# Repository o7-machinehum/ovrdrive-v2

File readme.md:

Phantomdrive is open source encrypted USB drive with a stealth mechanism to hide its second partition. To decrypt it you must create a file called unlock.txt containing your password in the format `password:addpasswordhere`, this is used to derive a AES-256 key. The drive automatically unmounts itself, remounts the remaining disk and encrypts and decrypts in place. It uses CH569W SoC, which has USB3, SDIO and an AES hardware block. It is programmable over USB using the `wch-ch56x-isp` library.

``` bash
|-- ee             # Hardware files
|-- Makefile
|-- readme.md      # This files
|-- test           # Test the cypto components
|-- ref            # Reference docs
|-- src            # Firmware
|-- tests          # Verification scripts
|-- wch-ch56x-bsp  # Board support package
`-- wch-ch56x-isp  # Programming software
```

# Getting Started
``` bash
git submodule update --init --recursive --checkout --force
cd wch-ch56x-isp
make # Build the ISP tool
```

## Install the toolchain
The HydraUSB3 project requires a patched GCC that supports the
`WCH-Interrupt-fast` interrupt attribute. Download the xpack GCC from the HydraUSB3 project:

```bash
cd /tmp
curl -sL -o riscv-gcc-xpack.tar.gz \
  "https://github.com/hydrausb3/riscv-none-elf-gcc-xpack/releases/download/12.2.0-1/xpack-riscv-none-elf-gcc-12.2.0-1-linux-x64.tar.gz"
tar xzf riscv-gcc-xpack.tar.gz
sudo cp -r xpack-riscv-none-elf-gcc-12.2.0-1/* /usr/local/
```

## Debugging
```
make UART=1 # Enable UART
make UART=1 DEBUG_USB=1 # Enable USB Debugging
```

## Build and Flashing the project
``` bash
make
# Remove flash drive
# While holding boot button, plug in
./wch-ch56x-isp/wch-ch56x-isp -d=off # This is needed just one to disable debug mode
make flash
```

## Unlocking Drive
``` bash
sudo echo "password:YourPasswordHere13245" > /mnt/unlock.txt
```

# Releasing the hardware
``` bash
./scripts/release_hardware.sh
```

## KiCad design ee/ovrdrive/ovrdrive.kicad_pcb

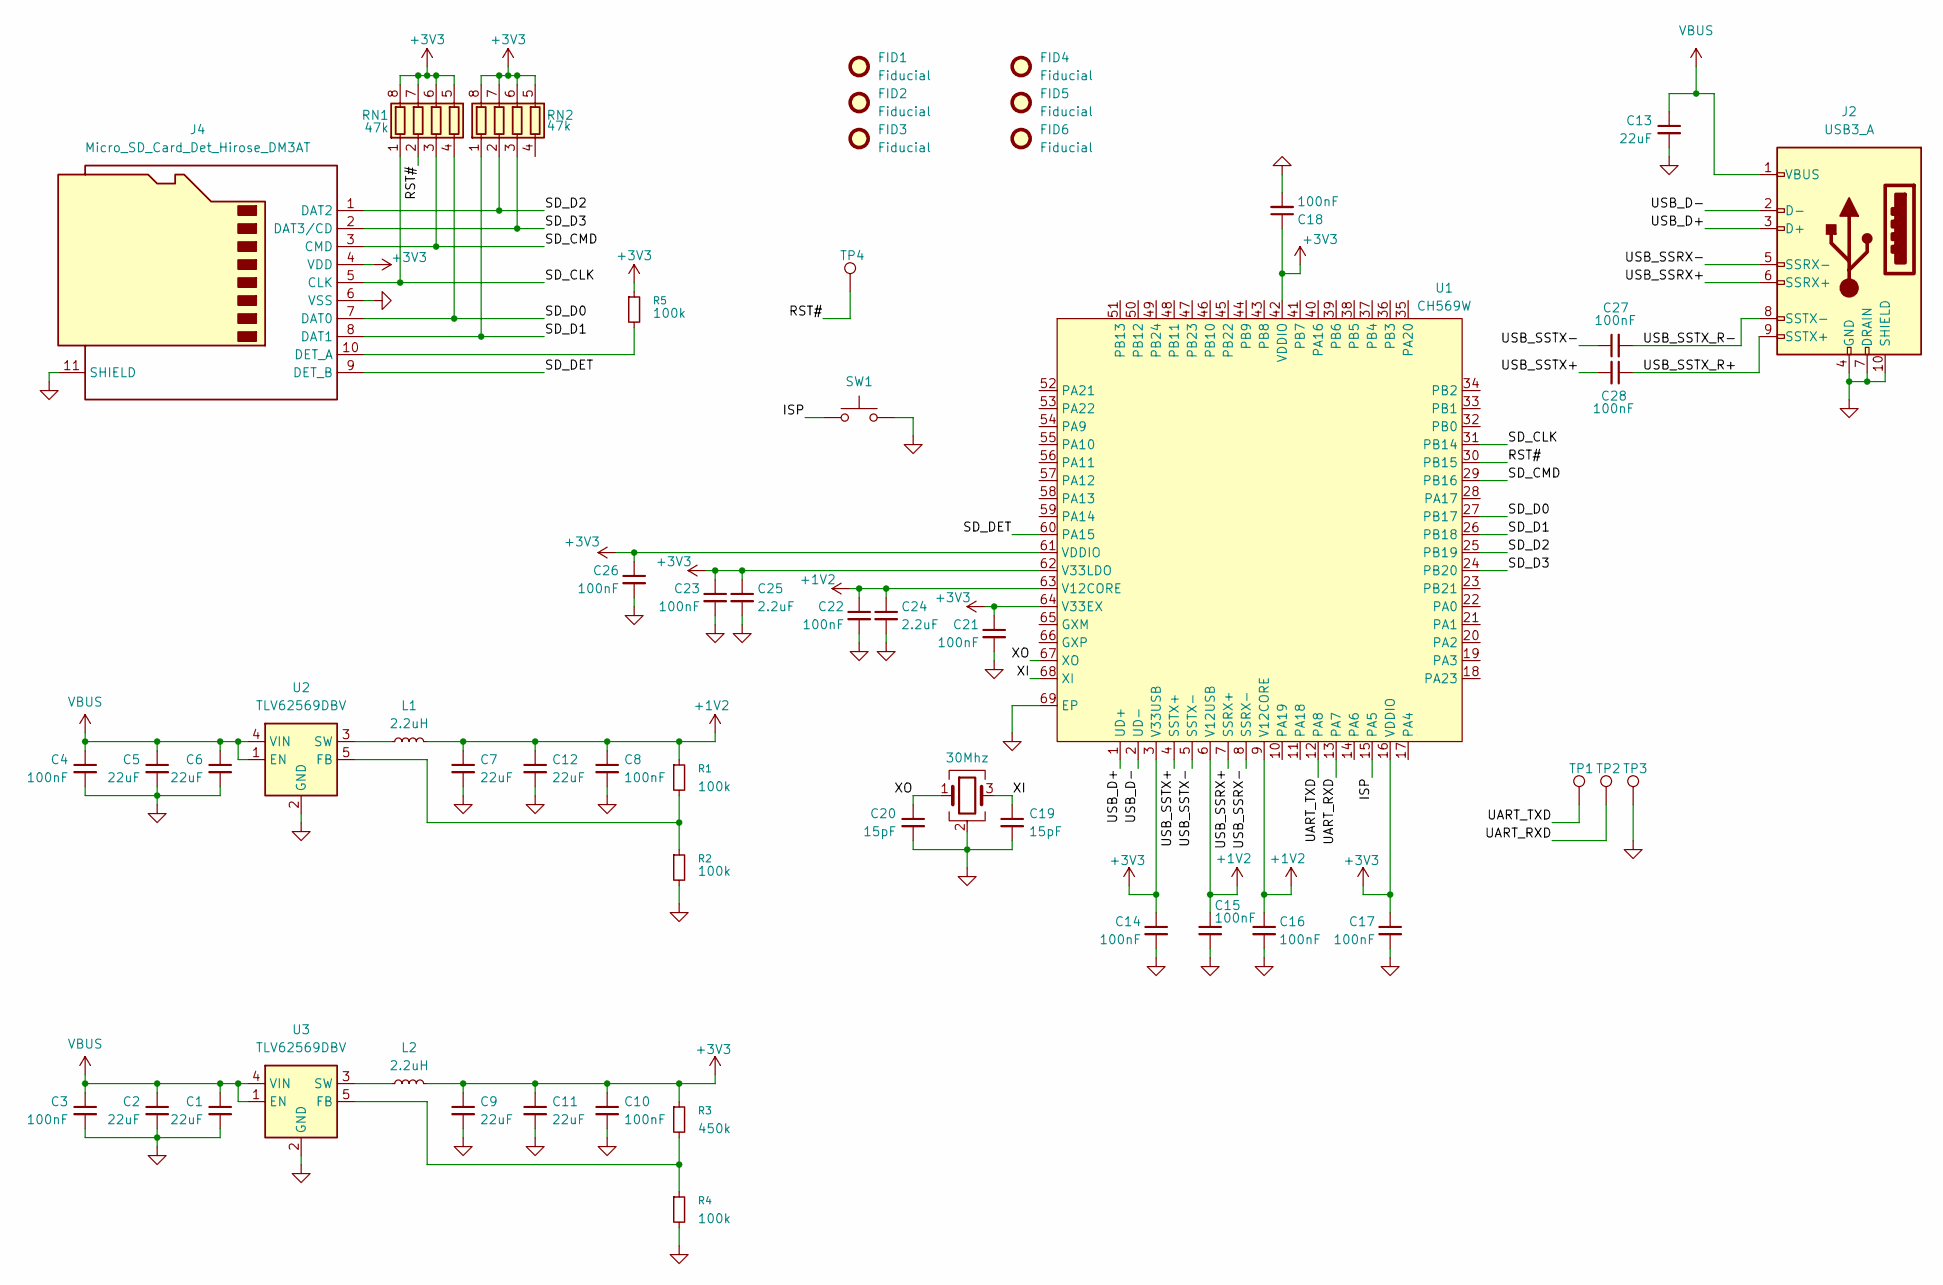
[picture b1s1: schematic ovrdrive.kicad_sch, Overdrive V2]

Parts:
C1, C2, C5, C6, C7, C9, C11, C12, C13: 22uF; C_0402_1005Metric; MPN CL05A226MQ5N6J8
C3, C4, C8, C10, C14, C15, C16, C17, C18, C21, C22, C23, C26, C27, C28: 100nF; C_0402_1005Metric; MPN CL05B104KP5NNNC
C19, C20: 15pF; C_0402_1005Metric; MPN CL05C150JB5NNNC
C24, C25: 2.2uF; C_0402_1005Metric; MPN CL05A225MQ5NNNC
FID1, FID2, FID3, FID4, FID5, FID6: Fiducial; Fiducial_0.5mm_Mask1mm; MPN DNP
J2: USB3_A; USB3_A_Plug_Wuerth_692112030100_Horizontal; MPN 692112030100
J4: Micro_SD_Card_Det_Hirose_DM3AT; microSD_HC_Hirose_DM3AT-SF-PEJM5; MPN DM3AT-SF-PEJM5
L1, L2: 2.2uH; L_Changjiang_FTC303015D; MPN SRN3015-2R2M
R1, R2, R4, R5: 100k; C_0402_1005Metric; MPN RC0402FR-07100KL
R3: 450k; C_0402_1005Metric; MPN RC0402FR-07453KL
RN1, RN2: 47k; R_Array_Concave_4x0402; MPN CAT10-473J4LF
SW1: SW_Push; SW_Push_SPST_NO_Alps_SKRK; MPN SKRKAEE020
TP1, TP2, TP3, TP4: TestPoint; TestPoint_Pad_1.0x1.0mm; MPN DNP
U1: CH569W; QFN-68-1EP_8x8mm_P0.4mm_EP5.2x5.2mm; MPN CH569W
U2, U3: TLV62569DBV; SOT-23-5; MPN TLV62569DBV
Y2: 30Mhz; Crystal_SMD_3225-4Pin_3.2x2.5mm; MPN ABM8-30.000MHZ-12-B1U-T

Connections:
+1V2: C7.1, C8.1, C12.1, C15.1, C16.1, C22.1, C24.1, L1.2, R1.1, U1.6 (V12USB), U1.9 (V12CORE), U1.63 (V12CORE)
+3V3: C9.1, C10.1, C11.1, C14.1, C17.1, C18.1, C21.1, C23.1, C25.1, C26.1, J4.4 (VDD), L2.2, R3.1, R5.1, RN1.5 (R4.2), RN1.6 (R3.2), RN1.7 (R2.2), RN1.8 (R1.2), RN2.5 (R4.2), RN2.6 (R3.2), RN2.7 (R2.2), RN2.8 (R1.2), U1.3 (V33USB), U1.16 (VDDIO), U1.42 (VDDIO), U1.61 (VDDIO), U1.62 (V33LDO), U1.64 (V33EX)
/ISP: SW1.1, U1.15 (PA5)
/RST#: RN1.2 (R2.1), TP4.1 (1_1), U1.30 (PB15)
/SD_CLK: J4.5 (CLK), RN1.1 (R1.1), U1.31 (PB14)
/SD_CMD: J4.3 (CMD), RN1.3 (R3.1), U1.29 (PB16)
/SD_D0: J4.7 (DAT0), RN1.4 (R4.1), U1.27 (PB17)
/SD_D1: J4.8 (DAT1), RN2.1 (R1.1), U1.26 (PB18)
/SD_D2: J4.1 (DAT2), RN2.2 (R2.1), U1.25 (PB19)
/SD_D3: J4.2 (DAT3/CD), RN2.3 (R3.1), U1.24 (PB20)
/SD_DET: J4.9 (DET_B), U1.60 (PA15)
/UART_RXD: TP2.1 (1_1), U1.13 (PA7)
/UART_TXD: TP1.1 (1_1), U1.12 (PA8)
/USB_D+: J2.3 (D+), U1.1 (UD+)
/USB_D-: J2.2 (D-), U1.2 (UD-)
/USB_SSRX+: J2.6 (SSRX+), U1.7 (SSRX+)
/USB_SSRX-: J2.5 (SSRX-), U1.8 (SSRX-)
/USB_SSTX+: C28.2, U1.4 (SSTX+)
/USB_SSTX-: C27.1, U1.5 (SSTX-)
/USB_SSTX_R+: C28.1, J2.9 (SSTX+)
/USB_SSTX_R-: C27.2, J2.8 (SSTX-)
/XI: C19.1, U1.68 (XI), Y2.3
/XO: C20.1, U1.67 (XO), Y2.1
GND: C1.2, C2.2, C3.2, C4.2, C5.2, C6.2, C7.2, C8.2, C9.2, C10.2, C11.2, C12.2, C13.2, C14.2, C15.2, C16.2, C17.2, C18.2, C19.2, C20.2, C21.2, C22.2, C23.2, C24.2, C25.2, C26.2, J2.4 (GND), J2.7 (DRAIN), J2.10 (SHIELD), J4.6 (VSS), J4.11 (SHIELD), R2.2, R4.2, SW1.2, TP3.1 (1_1), U1.69 (EP), U2.2 (GND), U3.2 (GND), Y2.2 (G), Y2.4 (G)
unnamed: J4.10 (DET_A), R5.2
unnamed: R1.2, R2.1, U2.5 (FB)
unnamed: L1.1, U2.3 (SW)
unnamed: R3.2, R4.1, U3.5 (FB)
unnamed: L2.1, U3.3 (SW)
VBUS: C1.1, C2.1, C3.1, C4.1, C5.1, C6.1, C13.1, J2.1 (VBUS), U2.1 (EN), U2.4 (VIN), U3.1 (EN), U3.4 (VIN)

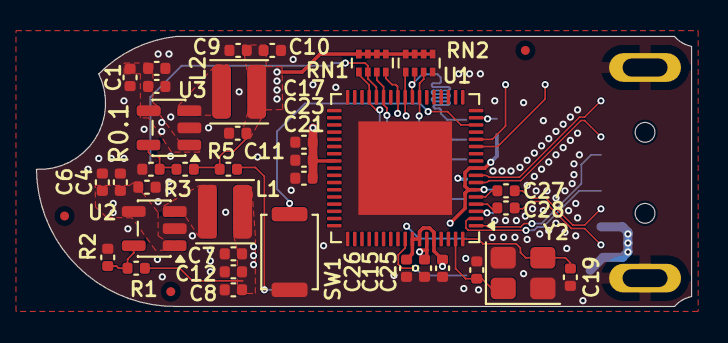
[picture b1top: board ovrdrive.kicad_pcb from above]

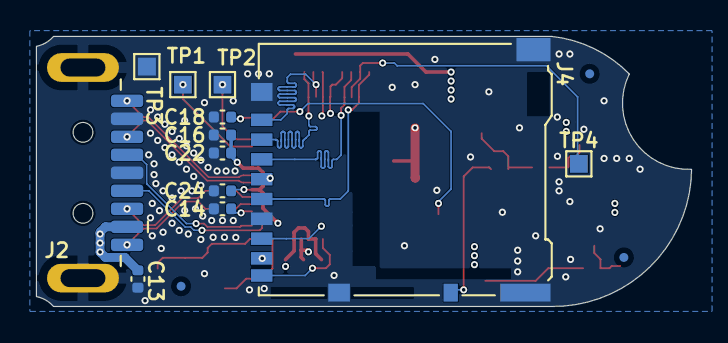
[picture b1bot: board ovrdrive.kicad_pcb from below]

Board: 4 copper layers, 36.4 x 15.0 mm, 54 parts (15 on the bottom side), 30 nets.

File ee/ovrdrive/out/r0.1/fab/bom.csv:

"Designator","Value","Footprint","Quantity","Part Number"
"C1,C2,C5-C7,C9,C11-C13","22uF","Capacitor_SMD:C_0402_1005Metric","9","CL05A226MQ5N6J8"
"C3,C4,C8,C10,C14-C18,C21-C23,C26-C28","100nF","Capacitor_SMD:C_0402_1005Metric","15","CL05B104KP5NNNC"
"C19,C20","15pF","Capacitor_SMD:C_0402_1005Metric","2","CL05C150JB5NNNC"
"C24,C25","2.2uF","Capacitor_SMD:C_0402_1005Metric","2","CL05A225MQ5NNNC"
"J2","USB3_A","Connector_USB:USB3_A_Plug_Wuerth_692112030100_Horizontal","1","692112030100"
"J4","Micro_SD_Card_Det_Hirose_DM3AT","Connector_Card:microSD_HC_Hirose_DM3AT-SF-PEJM5","1","DM3AT-SF-PEJM5"
"L1,L2","2.2uH","Inductor_SMD:L_Changjiang_FTC303015D","2","SRN3015-2R2M"
"R1,R2,R4,R5","100k","Capacitor_SMD:C_0402_1005Metric","4","RC0402FR-07100KL"
"R3","450k","Capacitor_SMD:C_0402_1005Metric","1","RC0402FR-07453KL"
"RN1,RN2","47k","Resistor_SMD:R_Array_Concave_4x0402","2","CAT10-473J4LF"
"SW1","SW_Push","Button_Switch_SMD:SW_Push_SPST_NO_Alps_SKRK","1","SKRKAEE020"
"U1","CH569W","Package_DFN_QFN:QFN-68-1EP_8x8mm_P0.4mm_EP5.2x5.2mm","1","CH569W"
"U2,U3","TLV62569DBV","Package_TO_SOT_SMD:SOT-23-5","2","TLV62569DBV"
"Y2","30Mhz","Crystal:Crystal_SMD_3225-4Pin_3.2x2.5mm","1","ABM8-30.000MHZ-12-B1U-T"

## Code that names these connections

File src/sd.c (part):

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 * (CMD17/18 for read, CMD24/25 for write).
 *
 * Hardware interface:
 *   CLK  = PB15 (bSDCK)          - SD clock output
 *   CMD  = PB14 (bSDCMD)         - SD command line (bidirectional)
 *   DAT0 = PB17                  - SD data line 0
 *   DAT1 = PB18                  - SD data line 1
 *   DAT2 = PB19                  - SD data line 2
 *   DAT3 = PB20                  - SD data line 3
 *   [CH569DS1.PDF: GPIO Pin Multiplexing, eMMC Controller]
 *
 * Clock configuration:
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	/* GPIO: Enable pull-ups on CMD and DAT lines for proper idle state
	 * SD spec requires pull-ups on CMD, DAT0-DAT3 */
	R32_PB_PU  |= bSDCMD;        /* CMD line pull-up */
	R32_PB_PU  |= (0x1f<<17);    /* DAT0-DAT4 pull-ups (PB17-PB21) */
	R32_PA_PU  |= (7<<0);        /* Additional data lines (PA0-PA2) */
	R32_PB_DIR |= bSDCK;         /* CLK line as output */

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
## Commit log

2026-03-07 Inital commit, MSD working.
2026-03-07 Added proper CR's, added a clangd file.
2026-03-07 MSD works, issues with device showing up as disk.
2026-03-07 MSD working, issues sorted out
2026-03-25 MSD *actually* working this time.
2026-03-25 Increased SD clock speed (getting around 20MB/s) and unset debug flag.
2026-03-26 The disk encryption worked once, but now trying again it didn't.
2026-03-26 Scrub the password from the unlock.txt file write.
2026-03-26 Added reference material.
2026-03-29 Added ee files for drive.
2026-03-29 Added some docs to the readme.
2026-03-29 typo
2026-03-29 Finished routing of PCB.
2026-03-29 Added release script
2026-03-29 Readded testing scripts.
2026-03-29 Added a script to create hardware releases.
2026-03-29 Fixed SDIO pinout, length matched SDIO traces.
2026-04-21 Added mech files (from overdrive r1), refactored source code, released r0.1 PCB (at fab)
2026-04-21 Added tests to test our sha256 function
2026-04-21 Docs
2026-05-01 Added image
2026-05-01 Formatting
2026-05-01 Removed some old notes.
2026-05-01 Logo change
2026-05-01 Logo changes again.
2026-05-01 Cleaned up, added proper build targets for debugging, logging cleaned up.
2026-05-13 Gated debug things behind debug flag.
2026-05-13 Increated SD card clock speed.
2026-05-13 Readme change
2026-05-14 Instrument eMMC write latency and gate CMD24 writes

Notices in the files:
src/sd.c:
SPDX-License-Identifier: Apache-2.0
